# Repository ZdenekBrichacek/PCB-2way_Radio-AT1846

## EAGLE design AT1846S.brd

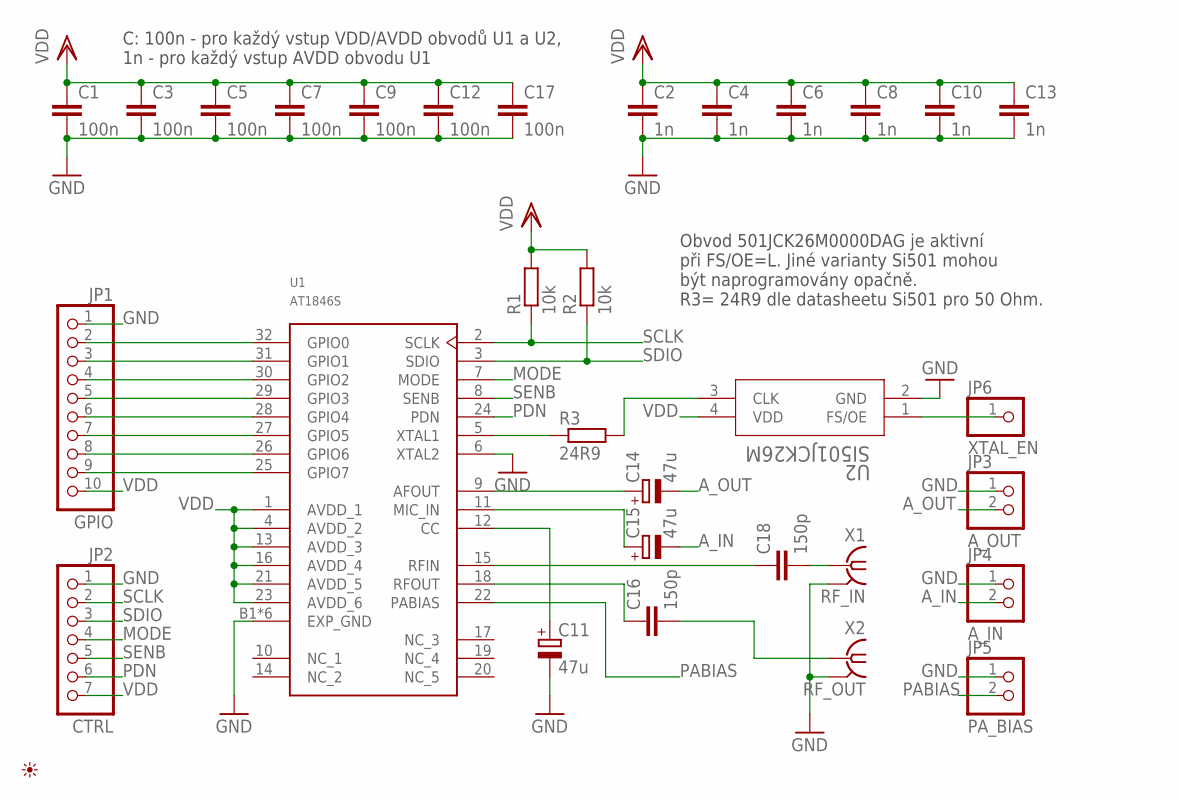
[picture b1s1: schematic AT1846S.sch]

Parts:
C1, C3, C5, C7, C9, C12, C17: 100n; C0603
C2, C4, C6, C8, C10, C13: 1n; C0603
C11, C14, C15: 47u; SMC_A
C16, C18: 150p; C0603
JP1: GPIO; 1X10
JP2: CTRL; 1X07
JP3: A_OUT; 1X02
JP4: A_IN; 1X02
JP5: PA_BIAS; 1X02
JP6: XTAL_EN; 1X01
PICTO1: PICTO_1
R1, R2: 10k; R0603
R3: 24R9; R0603
U1: AT1846S; QFN32
U2: SI501JCK26M; SI501_4_2X2.5
X1: RF_IN; J502-ND-142-0701-801/806
X2: RF_OUT; J502-ND-142-0701-801/806

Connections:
A_IN: C15.-, JP4.2
A_OUT: C14.-, JP3.2
GND: C1.2, C2.2, C3.2, C4.2, C5.2, C6.2, C7.2, C8.2, C9.2, C10.2, C11.-, C12.2, C13.2, C17.2, JP1.1, JP2.1, JP3.1, JP4.1, JP5.1, U1.6 (XTAL2), U1.B1 (EXP_GND), U1.B2 (EXP_GND), U1.B3 (EXP_GND), U1.B4 (EXP_GND), U1.B5 (EXP_GND), U1.EXP (EXP_GND), U2.2 (GND), X1.G@1 (2), X1.G@2 (2), X1.G@3 (2), X1.G@4 (2), X2.G@1 (2), X2.G@2 (2), X2.G@3 (2), X2.G@4 (2)
MODE: JP2.4, U1.7 (MODE)
unnamed: C11.+, U1.12 (CC)
unnamed: C14.+, U1.9 (AFOUT)
unnamed: C15.+, U1.11 (MIC_IN)
unnamed: C16.1, U1.18 (RFOUT)
unnamed: C18.1, U1.15 (RFIN)
unnamed: R3.2, U2.3 (CLK)
unnamed: JP6.1, U2.1 (FS/OE)
unnamed: JP1.2, U1.32 (GPIO0)
unnamed: JP1.3, U1.31 (GPIO1)
unnamed: JP1.4, U1.30 (GPIO2)
unnamed: JP1.5, U1.29 (GPIO3)
unnamed: JP1.6, U1.28 (GPIO4)
unnamed: JP1.7, U1.27 (GPIO5)
unnamed: JP1.8, U1.26 (GPIO6)
unnamed: JP1.9, U1.25 (GPIO7)
unnamed: C16.2, X2.1
unnamed: R3.1, U1.5 (XTAL1)
unnamed: C18.2, X1.1
PABIAS: JP5.2, U1.22 (PABIAS)
PDN: JP2.6, U1.24 (PDN)
SCLK: JP2.2, R1.1, U1.2 (SCLK)
SDIO: JP2.3, R2.1, U1.3 (SDIO)
SENB: JP2.5, U1.8 (SENB)
VDD: C1.1, C2.1, C3.1, C4.1, C5.1, C6.1, C7.1, C8.1, C9.1, C10.1, C12.1, C13.1, C17.1, JP1.10, JP2.7, R1.2, R2.2, U1.1 (AVDD_1), U1.4 (AVDD_2), U1.13 (AVDD_3), U1.16 (AVDD_4), U1.21 (AVDD_5), U1.23 (AVDD_6), U2.4 (VDD)

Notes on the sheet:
C: 100n - pro každý vstup VDD/AVDD obvodů U1 a U2, 1n - pro každý vstup AVDD obvodu U1
Obvod 501JCK26M0000DAG je aktivní při FS/OE=L. Jiné varianty Si501 mohou být naprogramovány opačně. R3= 24R9 dle datasheetu Si501 pro 50 Ohm.

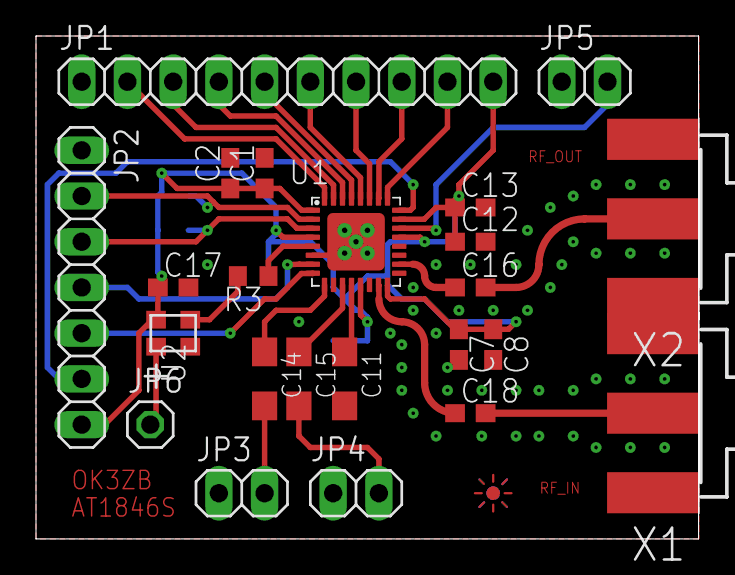
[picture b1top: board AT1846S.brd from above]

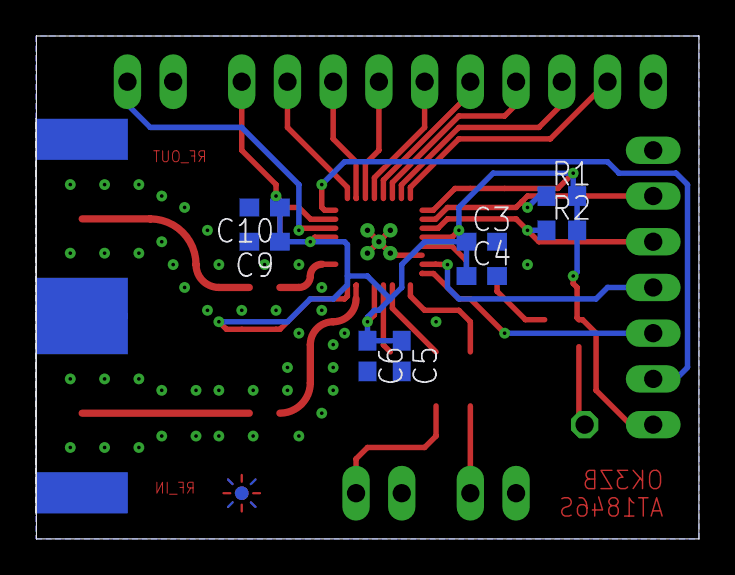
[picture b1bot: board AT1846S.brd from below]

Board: 2 copper layers, 36.8 x 27.9 mm, 32 parts (8 on the bottom side), 28 nets.

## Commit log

2017-10-10 :space_invader: Added .gitattributes & .gitignore files
2017-10-10 Initial version
